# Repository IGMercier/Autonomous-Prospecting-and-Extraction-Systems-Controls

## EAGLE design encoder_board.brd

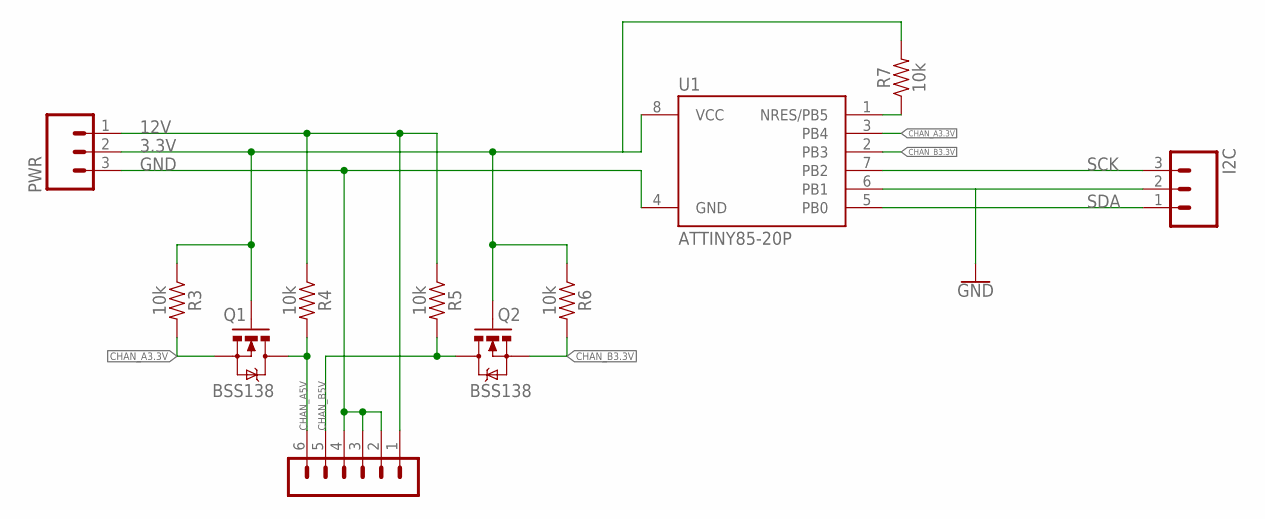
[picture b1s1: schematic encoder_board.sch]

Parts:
ENCODER: B6B-EH-A
I2C: CONN_03JST-PTH-VERT; JST-3-PTH-VERT
PWR: CONN_03JST-PTH-VERT; JST-3-PTH-VERT
Q1, Q2: BSS138; SOT23-3
R3, R4, R5, R6, R7: 10k; AXIAL-0.3
U1: ATTINY85-20P; PDIP08_300MIL

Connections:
3.3V: PWR.2, Q1.1 (G), Q2.1 (G), R3.P$1 (1), R6.P$1 (1), R7.P$2 (2), U1.8 (VCC)
12V: ENCODER.1, PWR.1, R4.P$1 (1), R5.P$1 (1)
CHAN_A3.3V: Q1.2 (S), R3.P$2 (2), U1.3 (PB4)
CHAN_A5V: ENCODER.6, Q1.3 (D), R4.P$2 (2)
CHAN_B3.3V: Q2.2 (S), R6.P$2 (2), U1.2 (PB3)
CHAN_B5V: ENCODER.5, Q2.3 (D), R5.P$2 (2)
GND: ENCODER.2, ENCODER.3, ENCODER.4, I2C.2, PWR.3, U1.4 (GND), U1.6 (PB1)
unnamed: R7.P$1 (1), U1.1 (NRES/PB5)
SCK: I2C.3, U1.7 (PB2)
SDA: I2C.1, U1.5 (PB0)

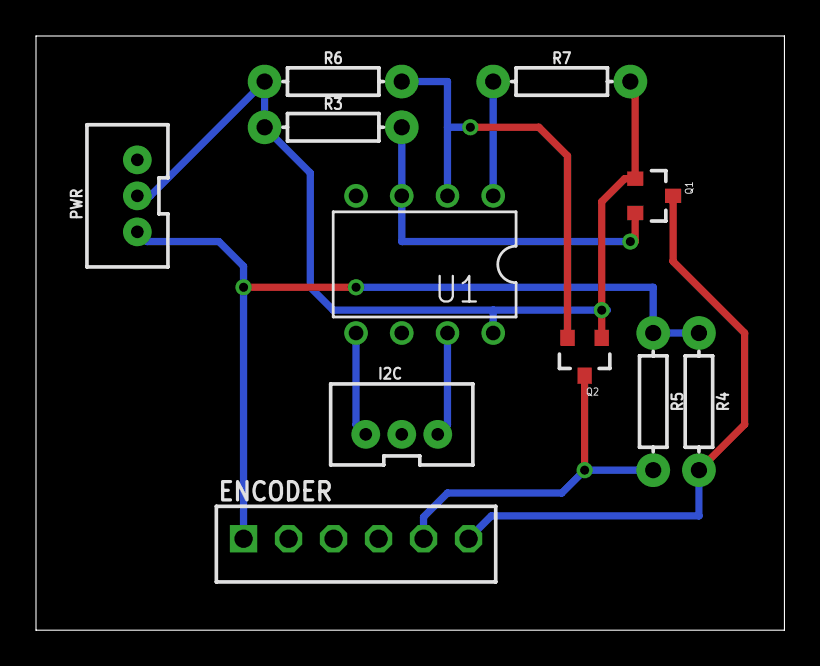
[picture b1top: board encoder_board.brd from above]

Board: 2 copper layers, 41.6 x 33.0 mm, 11 parts (0 on the bottom side), 10 nets.

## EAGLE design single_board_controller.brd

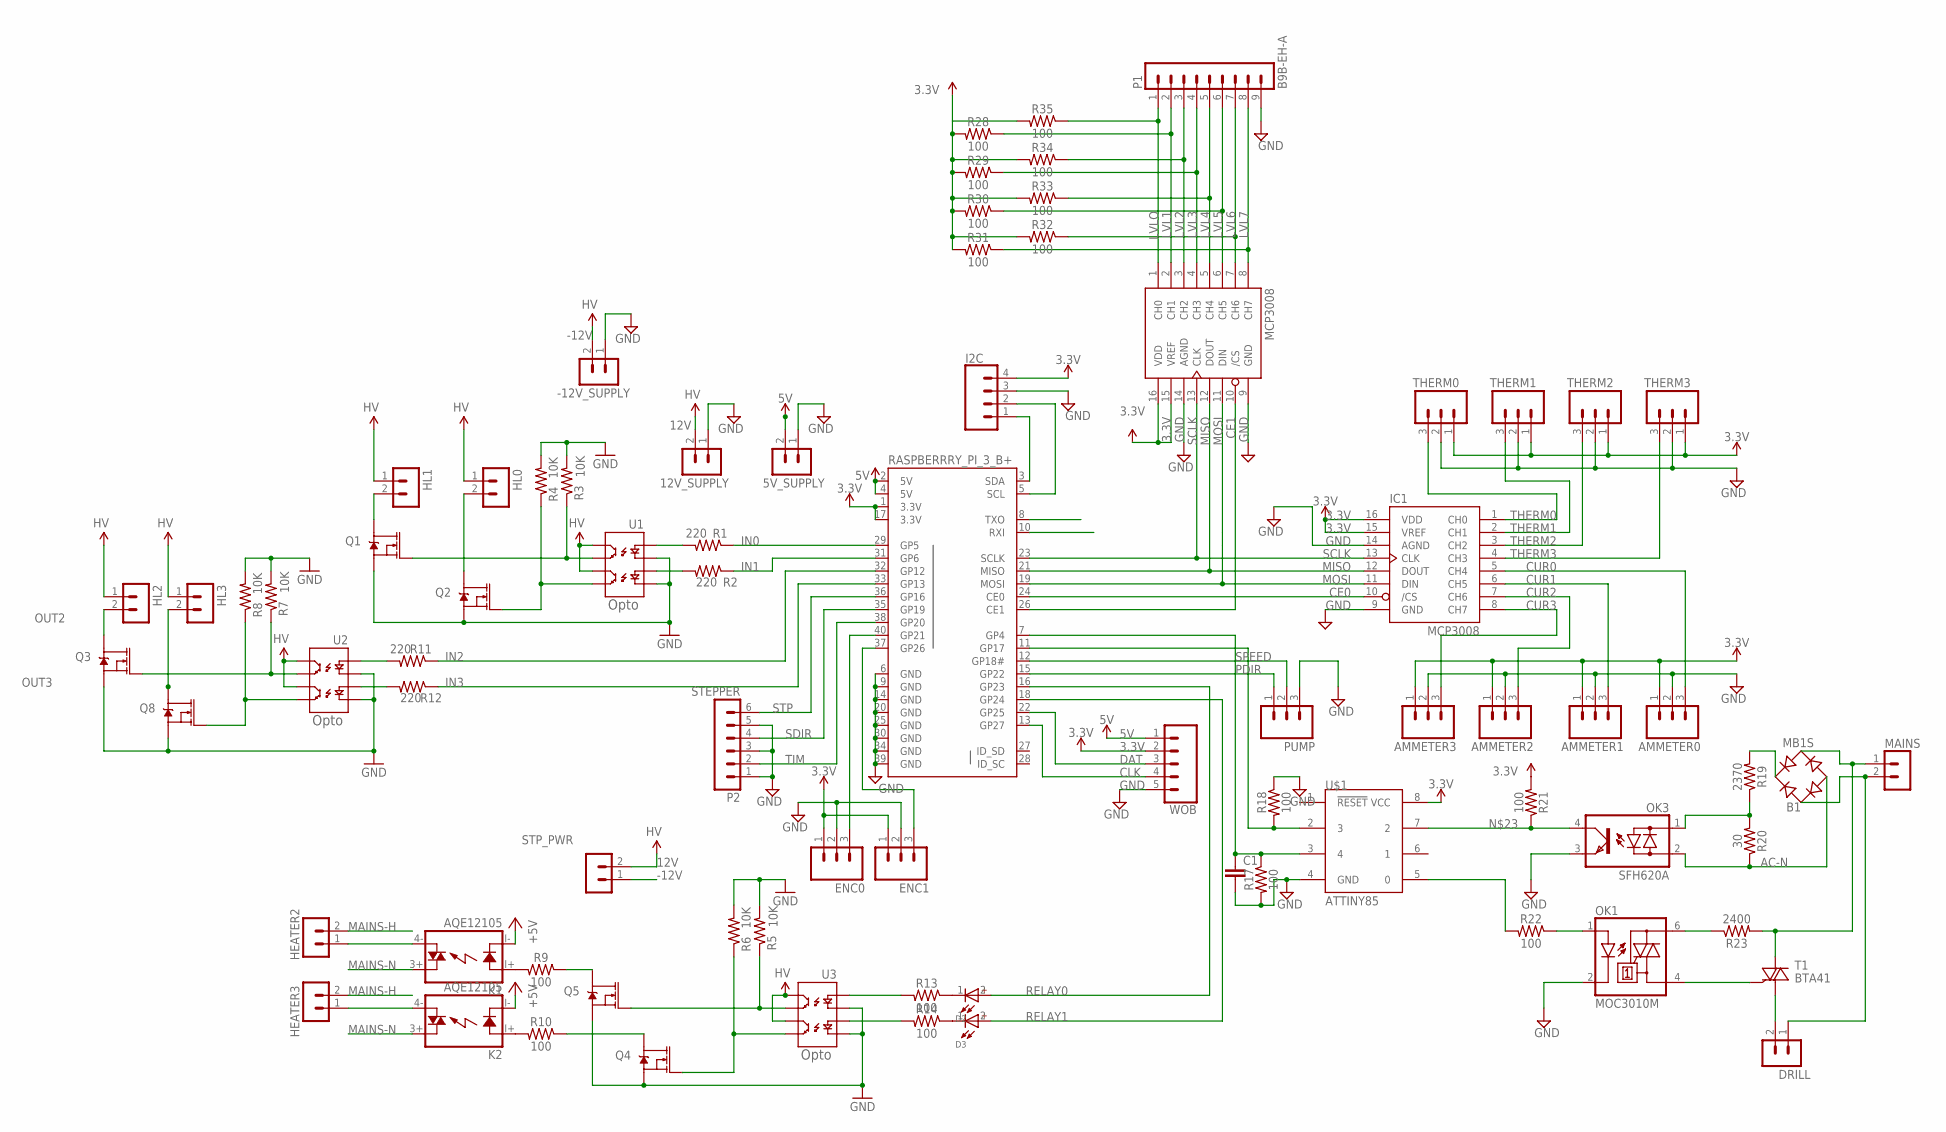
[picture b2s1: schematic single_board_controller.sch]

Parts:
5V_SUPPLY, 12V_SUPPLY: B2P-VH
-12V_SUPPLY: B2P-VH
AMMETER0, AMMETER1, AMMETER2, AMMETER3: CONN_03JST-PTH-VERT; JST-3-PTH-VERT
B1: MB1S; SOIC-4
C1: C; C0805
D2, D3: WL-SMRW_1206_156120YS75000-Y; WL-SMRW-1206-RECT
DRILL: B2P-VH
ENC0, ENC1: CONN_03JST-PTH-VERT; JST-3-PTH-VERT
HEATER2, HEATER3: B2P-VH
HL0, HL1, HL2, HL3: B2P-VH
I2C: CONN_04JST-PTH-VERT; JST-4-PTH-VERT
IC1, IC2: MCP3008; DIL16
K1, K2: AQE12105; AQE
MAINS: B2P-VH
OK1: MOC3010M; DIL06
OK3: SFH620A; DIL04
P1: B9B-EH-A
P2: STEPPER; B6B-EH-A
PUMP: CONN_03JST-PTH-VERT; JST-3-PTH-VERT
Q1, Q2, Q3, Q4, Q5, Q8: 35A/25V/8.5mΩ; DPAK
R1, R2, R11, R12: 220; 0603-RES
R3, R4, R5, R6, R7, R8: 10K; 0603-RES
R9, R10, R13, R14, R17, R18, R21, R22, R28, R29, R30, R31, R32, R33, R34, R35: 100; 0805
R19: 2370; 0805
R20: 30; 0805
R23: 2400; 0805
RASPBERRRY_PI_3_B+: RASPBERRYPI-40-PIN-GPIO_PTH_NO_SHROUD; 2X20
STP_PWR: B2P-VH
T1: BTA41; TOP3S-1
THERM0, THERM1, THERM2, THERM3: CONN_03JST-PTH-VERT; JST-3-PTH-VERT
U1, U2, U3: OPTOISOLATOR-2SOIC8; SO08-2
U$1: ATTINY85; 8P3
WOB: CONN_05JST-VERT; JST-5-PTH-VERT

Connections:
3.3V: AMMETER0.1, AMMETER1.1, AMMETER2.1, AMMETER3.1, ENC0.1, ENC1.1, I2C.4, IC1.15 (VREF), IC1.16 (VDD), IC2.15 (VREF), IC2.16 (VDD), R21.2, R28.2, R29.2, R30.2, R31.2, R32.2, R33.2, R34.2, R35.2, RASPBERRRY_PI_3_B+.1 (3.3V), RASPBERRRY_PI_3_B+.17 (3.3V), THERM0.1, THERM1.1, THERM2.1, THERM3.1, U$1.8 (VCC), WOB.2
5V: 5V_SUPPLY.2, RASPBERRRY_PI_3_B+.2 (5V), RASPBERRRY_PI_3_B+.4 (5V), WOB.1
-12V: -12V_SUPPLY.2, STP_PWR.1
AC-N: B1.-, OK3.2 (AC2), R20.1
CE0: IC1.10 (/CS), RASPBERRRY_PI_3_B+.24 (CE0)
CE1: IC2.10 (/CS), RASPBERRRY_PI_3_B+.26 (CE1)
CLK: RASPBERRRY_PI_3_B+.13 (GP27), WOB.4
CONTROL: R18.2, RASPBERRRY_PI_3_B+.11 (GP17), U$1.2 (3)
CUR0: AMMETER0.3, IC1.5 (CH4)
CUR1: AMMETER1.3, IC1.6 (CH5)
CUR2: AMMETER2.3, IC1.7 (CH6)
CUR3: AMMETER3.3, IC1.8 (CH7)
DAT: RASPBERRRY_PI_3_B+.22 (GP25), WOB.3
GND: 5V_SUPPLY.1, 12V_SUPPLY.1, -12V_SUPPLY.1, AMMETER0.2, AMMETER1.2, AMMETER2.2, AMMETER3.2, C1.2, ENC0.2, ENC1.2, I2C.3, IC1.9 (GND), IC1.14 (AGND), IC2.9 (GND), IC2.14 (AGND), OK1.2 (C), OK3.3 (E), P1.9, P2.1, P2.3, P2.5, PUMP.3, Q1.3 (S), Q2.3 (S), Q3.3 (S), Q4.3 (S), Q5.3 (S), Q8.3 (S), R3.2, R4.2, R5.2, R6.2, R7.2, R8.2, R17.2, R18.1, RASPBERRRY_PI_3_B+.6 (GND), RASPBERRRY_PI_3_B+.9 (GND), RASPBERRRY_PI_3_B+.14 (GND), RASPBERRRY_PI_3_B+.20 (GND), RASPBERRRY_PI_3_B+.25 (GND), RASPBERRRY_PI_3_B+.30 (GND), RASPBERRRY_PI_3_B+.34 (GND), RASPBERRRY_PI_3_B+.39 (GND), THERM0.2, THERM1.2, THERM2.2, THERM3.2, U1.2 (C1), U1.4 (C2), U2.2 (C1), U2.4 (C2), U3.2 (C1), U3.4 (C2), U$1.4 (GND), WOB.5
IN0: R1.1, RASPBERRRY_PI_3_B+.29 (GP5)
IN1: R2.1, RASPBERRRY_PI_3_B+.31 (GP6)
IN2: R11.1, RASPBERRRY_PI_3_B+.32 (GP12)
IN3: R12.1, RASPBERRRY_PI_3_B+.33 (GP13)
LVL1: IC2.2 (CH1), P1.2, R28.1
LVL2: IC2.3 (CH2), P1.3, R34.1
LVL3: IC2.4 (CH3), P1.4, R29.1
LVL4: IC2.5 (CH4), P1.5, R33.1
LVL5: IC2.6 (CH5), P1.6, R30.1
LVL6: IC2.7 (CH6), P1.7, R32.1
LVL7: IC2.8 (CH7), P1.8, R31.1
LVLO: IC2.1 (CH0), P1.1, R35.1
MAINS-H: B1.~2 (AC2), HEATER2.2, HEATER3.2, MAINS.1, R23.2, T1.A2
MAINS-N: B1.~1 (AC1), DRILL.1, K1.3+ (DS1), K2.3+ (DS1), MAINS.2
MISO: IC1.12 (DOUT), IC2.12 (DOUT), RASPBERRRY_PI_3_B+.21 (MISO)
MOSI: IC1.11 (DIN), IC2.11 (DIN), RASPBERRRY_PI_3_B+.19 (MOSI)
unnamed: R1.2, U1.1 (A1)
unnamed: R2.2, U1.3 (A2)
unnamed: R11.2, U2.1 (A1)
unnamed: R12.2, U2.3 (A2)
unnamed: ENC1.3, RASPBERRRY_PI_3_B+.37 (GP26)
unnamed: ENC0.3, RASPBERRRY_PI_3_B+.40 (GP21)
unnamed: OK3.1 (AC1), R19.1, R20.2
unnamed: OK1.1 (A), R22.1
unnamed: OK1.6 (A2), R23.1
unnamed: OK1.4 (A1), T1.G
unnamed: DRILL.2, T1.A1
unnamed: HEATER2.1, K1.4- (DS2)
unnamed: D2.1 (-), R13.1
unnamed: K2.I+ (A), R10.2
unnamed: D3.1 (-), R14.1
unnamed: K1.I+ (A), R9.2
unnamed: HEATER3.1, K2.4- (DS2)
unnamed: R13.2, U3.1 (A1)
unnamed: OK3.4 (C), R21.1, U$1.7 (2)
unnamed: B1.+, R19.2
unnamed: R22.2, U$1.5 (0)
unnamed: I2C.2, RASPBERRRY_PI_3_B+.5 (SCL)
unnamed: C1.1, R17.1, RASPBERRRY_PI_3_B+.7 (GP4), U$1.3 (4)
unnamed: I2C.1, RASPBERRRY_PI_3_B+.3 (SDA)
unnamed: R14.2, U3.3 (A2)
unnamed: Q5.4 (D), R9.1
unnamed: Q4.4 (D), R10.1
OUT0: HL1.2, Q1.4 (D)
OUT1: HL0.2, Q2.4 (D)
OUT1N: Q1.1 (G), R3.1, U1.7 (EM1)
OUT1N1: Q3.1 (G), R7.1, U2.7 (EM1)
OUT2: HL2.2, Q3.4 (D)
OUT2N: Q2.1 (G), R4.1, U1.5 (EM2)
OUT2N1: Q8.1 (G), R8.1, U2.5 (EM2)
OUT3: HL3.2, Q8.4 (D)
PDIR: PUMP.1, RASPBERRRY_PI_3_B+.15 (GP22)
RELAY0: D2.2 (+), RASPBERRRY_PI_3_B+.16 (GP23)
RELAY1: D3.2 (+), RASPBERRRY_PI_3_B+.18 (GP24)
SCLK: IC1.13 (CLK), IC2.13 (CLK), RASPBERRRY_PI_3_B+.23 (SCLK)
SDIR: P2.4, RASPBERRRY_PI_3_B+.35 (GP19)
SPEED: PUMP.2, RASPBERRRY_PI_3_B+.12 (GP18#)
STP: P2.6, RASPBERRRY_PI_3_B+.36 (GP16)
THERM0: IC1.1 (CH0), THERM0.3
THERM1: IC1.2 (CH1), THERM1.3
THERM2: IC1.3 (CH2), THERM2.3
THERM3: IC1.4 (CH3), THERM3.3
TIM: P2.2, RASPBERRRY_PI_3_B+.38 (GP20)

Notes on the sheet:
Opto

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
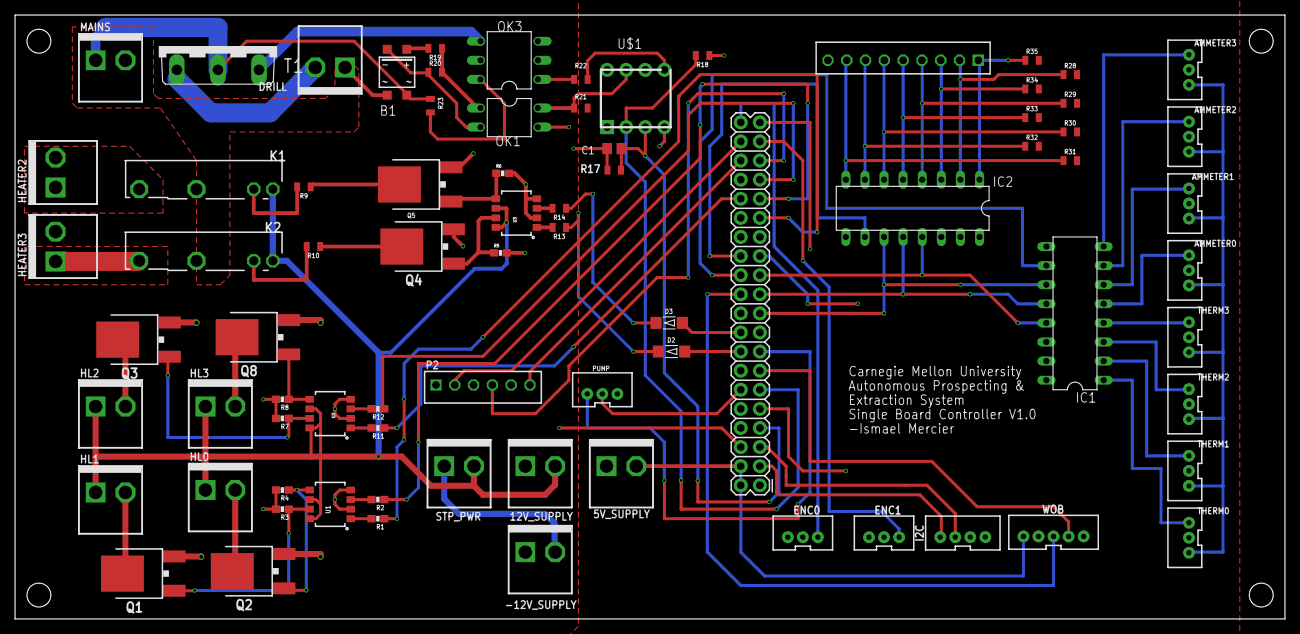
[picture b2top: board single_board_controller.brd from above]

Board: 2 copper layers, 168.9 x 80.3 mm, 78 parts (0 on the bottom side), 80 nets.

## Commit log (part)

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2019-01-20 Add files via upload
    initial commit
2019-01-20 added new design blocks, started Sensor board and outlined the missing parts
2019-01-26 Uploaded thermocouple amplifier design block
2019-01-26 Update MAX31856_thermocouple.dbl
    Added a voltage regulator because the sensor takes in 3.3V but our system is on 5V
2019-01-26 Uploaded MPR_pressure.dbl
    Breakout schematic for the temp barometric sensor (datasheet :https://sensing.honeywell.com/MPRLS0025PA00001A-amplified-board-mount-pressure-sensors), can be configured with I2C or SPI hardware
2019-03-19 new Single Board Driver
2019-03-19 placed the WOB header on brd, changed valve driver to two encoder headers, placed them on the brd
2019-03-20 begun placing high power connectors
2019-03-20 began adding 12V driver
2019-03-21 began cleaning up stencils
2019-03-21 added atiny85 drill driver, added mounting holes, isolated ground and 3.3V planes from AC, added I2C connector, still need to choose new mosfets, still need to verify AC circuitry, still need to pick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
2019-03-23 in process of replacing components
2019-03-30 already sent to fab, working on small improvements
2019-03-30 added src folder
2019-03-30 added load cells module bindings
2019-03-30 created APES system class
2019-03-31 added MCP3008 reading ability (test only)
2019-03-31 fixed Makefile
2019-03-31 removed time and spi members from APE class
2019-04-01 first draft encoder board schematic
2019-04-01 fixed huge bug: python interpreter exited after setup. @TODO: i need to provide better documentation...
2019-04-01 added some necessary docs
2019-04-02 added guards to make further debugging easier
2019-04-04 updated encoder board schematic
2019-04-04 created encoder board
2019-04-06 updated encoder_board sch
2019-04-06 updated headers in encoder_board sch
2019-04-13 This commit works, need to test header inclusions as to why...
2019-04-14 added bus param for measMCP3008
2019-04-14 added wiringPi initializer
2019-05-01 added base classes and methods for analog bus
2019-05-01 prepped shutdown if disconnected
2019-05-03 made changes to main.cpp
2019-05-04 cleaned things up, will make another branch for server stuff
2019-05-04 redid analog.c
2019-05-04 better integrated analog.cpp and APES.cpp
2019-05-04 added server-side code
2019-05-04 fixed a linker bug
2019-05-04 added some debug
2019-05-04 fixed port bug
2019-05-04 prepped server for command input and standby when disconnected
2019-05-04 refactored server.c to allow for better cmdline parsing
2019-05-04 added more commands
2019-05-04 added param to read_level
2019-05-05 fixed analog.h params
2019-05-05 implemented shutdown proceure
2019-05-05 added writeData method
2019-05-05 fixed file ptr error for debugging
2019-05-15 made load cell struct + funcs
2019-05-15 made free funcs
2019-05-15 added free func
2019-05-15 put wob_t in APES class
2019-05-15 need to refactor
2019-05-16 allowed only 1 client connection
2019-05-16 added retrys instead of exit on failure
2019-05-16 fixed method names
2019-05-16 added printouts for manual readings
2019-05-16 pushing all merges
2019-05-16 refactored components into one file
2019-05-16 refactored everything, following C++ allocation standard bc new and malloc dont like each other
2019-05-16 created a temp L298N python module
2019-05-16 added motor methods to main system class
2019-05-16 added motor func in server file
2019-05-16 created a dataPt class to store data/time info, maybe will be useful?
2019-05-16 cleaned up code
2019-05-16 prepped a readData func
2019-05-16 implemented parseline, needs to be fixed
2019-05-16 maybe perhaps figured out how to cast python value to c++ value?
2019-05-17 removed dependency on csapp.h, have to: finish server implementation, test server implementation, test commands
2019-05-18 reimplemented server/client functions, still getting a large bug where commands aren't being interpreted correctly
2019-05-19 making progress on refining the server
2019-05-19 fixed server bug, commands are recognized
2019-05-19 finally fixed the disconnect issue
2019-05-20 added pybind11 submodule
2019-05-20 added hx711py submodule
2019-05-20 removed submodules bc im dumb and forgot to fork them
2019-05-20 added time func to Motor method
2019-05-20 started working on the todo's i had
2019-05-20 made small changes, going to implement writeData/readData tmrw
2019-05-20 created a hacky write method, need to test
2019-05-20 rewrote write functions, added saveData function, put l298n in its own repo
2019-05-20 pushing good sever code for Jared
2019-05-20 this compiles, but dont run since some things are not initialized
2019-05-21 added debugging statements, I can't get past the initialization until we have actual sensing abililties
2019-05-21 put in threads for each sensor, I will need to refactor the whole server.cpp to designate foreground and background jobs :[
2019-05-21 changed headers
2019-05-21 added serverBase class
2019-05-21 implemented server classes, added main program file
2019-05-21 updated Makefile
2019-05-21 reorganized repo
2019-05-21 refactored, I need to add job states so that the system can distinguis between the manual and automatic commands
2019-05-21 added some headers to base server
2019-05-21 implemented setCommands and listCommands function
2019-05-21 prints connected ip address
2019-05-21 in the middle of testing, getting a segfault :[
2019-05-21 fixed the segfault bug :]
2019-05-22 fixed the TCP bug, but will haveto do heavier testing just in case
2019-05-22 removed some dead code
2019-05-22 set APES read func to return a dataPt*
2019-05-23 made some server changes
2019-05-23 switched to c++ threads
2019-05-23 commented out any functionality that does not pertain to servers, prepping to shift that into the shell class
2019-05-23 set up program.cpp
2019-05-23 in the middle of integrating, deleted commented out code, need to figure out how to stop the server thread
2019-05-23 added condition to kill server and shell threads
2019-05-23 reorganized
2019-05-23 changed server class names, moved command functions to APESShell
2019-05-23 fixed base parseline
2019-05-23 finally fixed parsing bug
2019-05-24 shell seems to be processing commands a-ok
2019-05-24 fixed some headers in shell and server
2019-05-24 in the middle of retesting server & shell
2019-05-24 added locks around fd read and writes
2019-05-24 fixed README
2019-05-24 server writes to file that shell reads from, server reads from file that shell writes to
2019-05-24 ugh i have a tcp buggg
2019-05-24 removed client-thread bc that was unnecessary...
2019-05-25 committing even though ive gotten no where
2019-05-25 committing for funsies
2019-05-25 verified shell works
2019-05-25 made setClientSockOpts func
2019-05-25 i think i figured this out
2019-05-25 had to put setServerSockOpts in while loop
2019-05-25 inserted write to cmd.txt
2019-05-25 added cmdfile member
2019-05-25 writes input to cmdfile
2019-05-25 put read into func
2019-05-25 put unique lock around file open
2019-05-25 reads from logfile
2019-05-25 commmtiing
2019-05-25 server needs to write or else hangup will occur
2019-05-25 moved locks out of loops
2019-05-26 made some changes
2019-05-26 fixed bug
2019-05-26 testing shell
2019-05-26 changed from reading from files to popping queues
2019-05-26 shell reads from cmd queue
2019-05-26 fixed server buf allocation
2019-05-26 tested shell and server, using deques was such a good idea
2019-05-26 cleaned up serverBase
2019-05-26 testing server + shell
2019-05-26 debugging stack smashing error
2019-05-26 commmting
2019-05-27 trying to figure out why adding the python configs causes a stack smashing detection
2019-05-27 put createClient in run func, does not stack smash
2019-05-27 receives user input and shell processes it, now going to figure out how to write to user
2019-05-27 client received data, but is kinda weirdly formatted
2019-05-27 found stack smashing bug
2019-05-28 cleaning up
2019-05-28 removed rio dependency
2019-05-28 removed rio from Makefile, testing new escape sequence
2019-05-28 added ServerBase::print
2019-05-28 implemented funcs to simulataneously read sensor data
2019-05-28 put (in comments) robot funcs in shell
2019-05-29 converted parse_token to use std::strings
2019-05-29 started implementation of Encoder class
2019-05-29 made auto funcs join instead of detachabe
2019-05-29 created data_mtx so that server can safely access data.csv
2019-05-30 fixed broken pipe bug
2019-05-30 added todo list to README
2019-05-30 fixed list in README
2019-05-30 fixed how data was printed to file
2019-05-30 added quick enum for autos, it isn't type-safe...
2019-05-30 fixed data_mtx
2019-05-30 made a sad-looking test and fixed program bug
2019-05-30 added help msg, it doesn't work tho
2019-05-30 added shutdown sig and removed write size+1
2019-05-30 added shutdown procedure + somehow that messed up with close on timeout..?
2019-05-30 i think the timeout was fine, i was just being dumb in my testing
2019-05-31 fixed bug, i hope the ugliness that is outputted is just a problem the client can solve
2019-05-31 Adding client files to git
2019-05-31 committing to implement Jared's idea
2019-05-31 this sucks
2019-05-31 committed to checkout
2019-05-31 have client test this
2019-05-31 Client can connect to server without crashing itself
2019-05-31 Added auto-reconnect functionality
2019-05-31 added motor_x and motor_y
2019-05-31 added new commits to l298n lib
2019-05-31 Ensured socket read thread will join
2019-06-01 Preliminary commit until server-client communication is finished
2019-06-01 final pcb and schematic for Single board controller
2019-06-01 pinout for raspberry pi
2019-06-01 committing changes to server even tho im gonna overwrite them with Jared's awesome code
2019-06-01 added pinout definitions and defined bus
2019-06-01 Split write into its own thread, re-added toSend
2019-06-01 Fixed server shutdown logic
2019-06-01 Server logic completed
2019-06-01 Client logic completed, changed file and window names
2019-06-02 made components woooooooooo
2019-06-02 added componenets and their commands to shell
2019-06-02 updated README todo list
2019-06-02 Updated Therm struct
2019-06-02 attiny85 Arduino code -- need to test
2019-06-02 implemented drill cycle
2019-06-02 pushing for funsies
2019-06-02 changed some params
2019-06-02 fixed drill cycle
2019-06-03 made component test
2019-06-03 removed submodule
2019-06-03 pushing for testing
2019-06-03 committing filed
2019-06-03 added encoder test, really need to figure out stepper
2019-06-03 Fixed second client connect issue
2019-06-03 Current testing
2019-06-03 sort of got stepper working, got pump working
2019-06-03 committing changes
2019-06-03 implemented data file read, encoder, pump, and drill commands
2019-06-03 shutdown procudure needs to be looked at
2019-06-04 Updated .gitignore, client logging, some formatting
2019-06-04 Verified shutdown logic, tabs replaced with spaces
2019-06-04 Corrected ammeter output
2019-06-04 made pump an extension of Motor class
2019-06-04 made auto func simpler supposedly
2019-06-04 fixed standby func
2019-06-04 Clientside input control test
2019-06-04 fixed calls to deconstructors
2019-06-04 'New' client info
2019-06-04 Client History
2019-06-05 Separation of data logging initialized
2019-06-05 Some help command changes, updated .gitignore
2019-06-05 Missed one on .gitignore
2019-06-05 added tinywires tests
2019-06-05 Timestamped logging, beginning data transfer
2019-06-05 Altered stepper functions for constant dc/frequency
2019-06-05 Whitespace issues, oops
2019-06-05 added tiny tests
2019-06-05 put auto mode in shell class
2019-06-05 fixed data logging
2019-06-05 fixed time func
2019-06-05 Client data logging update, may revert partial later
2019-06-05 Time function switcheroo
2019-06-05 added new commits to hx711 lib
2019-06-05 Reinserted count() in time calculations
2019-06-05 adding params to fix compilation errors
2019-06-06 Altering automatic sensing logic
2019-06-06 committing to pull
2019-06-06 supposedly fixed stepper motor func, testing generally
2019-06-06 made some changes, got segfault
2019-06-06 made some changes to catch seg
2019-06-06 added encoder/stepper test
2019-06-06 Added data logging

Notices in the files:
parts and their libraries:
con-jst-eh: Copyright (C) 2016, Bob Starr
SparkFun-Connectors: Licensing: Creative Commons ShareAlike 4.0 International - https://creativecommons.org/licenses/by-sa/4.0
Wurth_Elektronik_Optoelectronics_rev18a: Copyright: Würth Elektronik
